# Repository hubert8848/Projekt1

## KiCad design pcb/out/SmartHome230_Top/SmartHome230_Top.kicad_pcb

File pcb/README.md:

# ⚡ pcbforge — generator schematów i PCB dla KiCad (A→Z)

Profesjonalny przepływ projektowania PCB sterowany opisem układu: **ty mówisz co chcesz
→ powstaje schemat KiCad bez błędów → płytka z footprintami i rozmieszczeniem →
eksport do autoroutingu (Freerouting) → gotowy projekt do otwarcia w KiCad.**
Do tego interfejs **web**, w którym uczysz toolkit, jakie footprinty i reguły
rozmieszczania stosować na przyszłość.

```
opis (czat / YAML)  ─►  Design (model)  ─►  .kicad_sch  (ERC czyste)
                                          ─►  .kicad_pcb (footprinty + placement)
                                          ─►  .dsn       (Specctra → Freerouting)
                          ▲                                   │
                          └──── baza wiedzy (kb.json) ◄────────┘  uczenie z web
```

## Dlaczego to działa bez instalacji KiCada
Toolkit generuje **samowystarczalne pliki KiCad 7**: wbudowane symbole + footprinty
i **jawną listę sieci** w PCB. Dzięki temu projekt otwiera się bez brakujących bibliotek.
Poprawność strukturalną potwierdza biblioteka `kiutils` (realny parser formatu KiCad),
a spójność elektryczną — wbudowane **ERC/DRC-lite**.

## Routing — czy trzeba uciekać z KiCada? Nie.
- **Ręcznie:** interaktywny router KiCada (push-and-shove) jest topowy — do większości
  płytek wystarcza i daje najlepszą jakość.
- **Automatycznie:** KiCad nie ma własnego autoroutera, ale **Freerouting** (Java)
  integruje się przez `.dsn` → trasowanie → `.ses`. To standardowa darmowa droga.
- **Inny program** (Altium/Allegro) ma sens dopiero przy bardzo gęstych, szybkich
  projektach (BGA, DDR, impedancja kontrolowana). Dla prototypów: KiCad + Freerouting.

pcbforge **eksportuje gotowy `.dsn`** i potrafi uruchomić Freerouting. Wynik `.ses`
wczytujesz w KiCad: **PCB Editor → File → Import → Specctra Session**.

---

## Szybki start

```bash
cd pcb
pip install -r requirements.txt          # opcjonalne (web/walidacja/YAML)

# 1) Wygeneruj przykładową płytkę ESP32 (kod):
python -m boards.esp32_devboard

# 2) Albo z deklaratywnego speca:
python -m pcbforge.cli build specs/ESP32_DevBoard.json
python -m pcbforge.cli check specs/ESP32_DevBoard.json
python -m pcbforge.cli route specs/ESP32_DevBoard.json --passes 20   # wymaga freerouting.jar

# 3) Podgląd graficzny (SVG/PNG, bez KiCada):
python -m pcbforge.cli preview specs/SmartSwitch.json

# 4) Pełna produkcja przez prawdziwy KiCad (Gerbery + STEP + ERC/DRC):
bash scripts/setup_kicad.sh                 # instaluje kicad-cli (raz na środowisko)
python -m pcbforge.cli fab specs/SmartSwitch.json

# 5) Interfejs web (przegląd + uczenie + podgląd inline + produkcja):
python -m web.app      # http://127.0.0.1:5000
```

> **KiCad:** eksport Gerberów/STEP/SVG działa od KiCad 7. **ERC/DRC z linii poleceń
> wymaga KiCad ≥ 8** — bez niego używane są kontrole wbudowane (`checks.py` + `rules.py`).

Pliki lądują w `pcb/out/<NazwaPłytki>/` — otwórz `*.kicad_pro` w KiCad.

## Autorouting — Freerouting
```bash
# pobierz jar z https://github.com/freerouting/freerouting/releases
export FREEROUTING_JAR=/sciezka/freerouting.jar
python -m pcbforge.cli route specs/ESP32_DevBoard.json
# -> out/ESP32_DevBoard/ESP32_DevBoard.ses  (import w KiCad)
```

---

## Katalog części
Obecnie ~35 części (rozszerzalne w `pcbforge/library/catalog.py`):
- **Bierne/dyskretne:** R, C, CP (elektrolit), L (cewki + cewka mocy 6×6), FB (ferryt),
  F (bezpiecznik), Y (kwarc), LED, diody (D_Schottky, D_Rectifier, D_TVS/ESD),
  tranzystory/MOSFETy (Q_NPN/PNP/NMOS/PMOS).
- **Układy:** ESP32-WROOM-32, AMS1117-3.3/5.0, MP1584 (buck), MCP23017 (ekspander I²C 16 IO),
  24LCxx (EEPROM), MAX485 (RS485), DS18B20 (czujnik temp 1-wire).
- **Złącza:** RJ45 8P8C, listwy zaciskowe, JST-XH, USB-C (zasilanie), USB Micro-B,
  gniazdo DC, goldpiny/sockety `Header_RxC` (też board-to-board), przyciski tact.
- **Obudowy footprintów:** chip 0402/0603/0805/1206, SOT-23-3/5/6, SOT-223, SOIC-8/14/16/28,
  TO-92, SMA/SOD-123/SOD-323, kwarc 3225 i in.

## Przykład: HomeController PRO — sterownik domowy 32 wej / 16 wyj
`boards/home_controller_pro.py` — pełny, realny produkt na 2 płytkach (24 V):
- **Dół:** zasilanie 24 V (bezpiecznik + dioda + MOV + buck 5 V + LDO 3V3), ekspander
  wyjść, **8× wyjście przekaźnikowe 230 V** + **8× wyjście MOSFET DC**, każde wyjście
  własny zacisk śrubowy; przekaźniki we wnętrzu (nie przy krawędzi).
- **Góra (węższa):** **ESP32-C3** + 2× ekspander I²C (**32 wejścia**), **8× RJ45** (wejścia,
  TVS na każde), **RS485 + CAN** (łączenie sterowników), złącze **TFT dotykowy**.
- Niezawodność „na 30 lat": TVS na każdym I/O, bezpiecznik + MOV, diody gasnące,
  pull-down bramek MOSFET, grube ścieżki + izolacja 230 V, dekapy, watchdog (ESP).

> ESP32-C3 ma mało GPIO — tu wykorzystane w pełni (USB do programowania, IO9 dzieli
> BOOT z CAN-RX). Pod pełną niezależność magistral rozważ **ESP32-S3**.

## Zasady rozmieszczania (urządzenia góra/dół, 230 V)
`boards/smart_home_230.py` + `pcbforge/layout.py` realizują zasady projektowe:
- **I/O na krawędziach** — złącza (USB-C, RJ45, zaciski) na górnej krawędzi; **strefa 230 V**
  (przekaźniki + zaciski sieciowe) na dolnej, z dala od logiki.
- **Otwory montażowe i złącze board-to-board w identycznych współrzędnych** na obu płytkach
  (wspólna `Frame`) — składają się 1:1.
- **Górna płytka węższa** o pasy I/O (góra/dół) — śrubokręt dochodzi do zacisków dolnej płytki
  (`Design.outline` = obszar środkowy).
- **Osobna dioda/TVS na każde I/O** (reguła `DIODE_PER_IO`).
- **230 V → grube ścieżki + izolacja**: sieci oznaczone `design.mark_mains(...)` dostają klasę
  `mains` w DSN (np. 1.5 mm / 2.5 mm creepage). Reguła `MAINS_UNMARKED` pilnuje oznaczenia.
- **Pasywne od spodu** — `c.side = "bottom"` (poprawne warstwy B.* + lustrzane pady).
- **Opisy po polsku** na silkscreenie (`Component.label`, `Design.notes`).

Nowe części: **przekaźnik SPDT** (szerokie pady 230 V), **otwór montażowy M3**, sterownik
przekaźnika (blok `relay_driver`: tranzystor + dioda gasnąca + rezystor bazy).

## Przykład: urządzenie dwupłytkowe (góra/dół)
`boards/home_controller.py` — **kontroler automatyki domowej z dwóch PCB** łączonych
listwą board-to-board 2×10 (wspólne mapowanie pinów `B2B_MAP`):
- **Dół** (`HomeCtrl_Bottom`): wejście 12 V (listwa) → bezpiecznik + dioda zabezpieczająca
  → **buck MP1584 (5 V)** z cewką/diodą/dzielnikiem → **LDO AMS1117 (3V3)** → **ESP32**.
- **Góra** (`HomeCtrl_Top`): listwa B2B → **MCP23017** (16 wejść przycisków) → **4× RJ45**
  (przyciski ścienne + 1-wire), **DS18B20** (temperatura), **ochrona ESD (TVS)** i pull-upy.

RJ45 użyte jako **złącze okablowania** (cat-kabel do włączników i czujnika), bez magnetyki/PHY.
Obie płytki: **ERC 0 błędów, 0 ostrzeżeń**, zwalidowane `kiutils`.

## Przykład: ESP32-WROOM-32 DevBoard
Pełny, realny układ wygenerowany end-to-end (`boards/esp32_devboard.py`):
zasilanie USB 5 V → LDO **AMS1117-3.3** → 3V3, kondensatory bulk + odsprzęgające,
pull-upy EN/IO0, przyciski **EN/BOOT**, LED statusu na IO2, header programatora
1×6 (GND/3V3/EN/IO0/TX/RX) i breakout GPIO 1×10. **ERC: 0 błędów, 0 ostrzeżeń.**

## Opis płytki w YAML/JSON
```yaml
name: Migacz_555
components:
  - {ref: U1, part: NE555, footprint: ... , connections: {...}}
  - {ref: R1, part: R, value: 10k, connections: {"1": VCC, "2": THR}}
```
(rdzeń biblioteki części rozszerza się w `pcbforge/library/catalog.py`)

## Uczenie (baza wiedzy)
W web, na stronie płytki:
- **Zmień footprint części** → zapis do `knowledge/kb.json`, stosowany przy kolejnych generacjach.
- **Reguła „near"** → „umieść C3 blisko U1 o 3 mm" (autoplacement to uwzględni, jeśli nie powoduje kolizji).
- **Notatki** → wskazówki na przyszłość.

---

## Architektura
| Plik | Rola |
|---|---|
| `pcbforge/model.py` | model: `Component`, `Net`, `Design`, reguły |
| `pcbforge/library/symbols.py` | generatory symboli schematu (geometria pinów) |
| `pcbforge/library/footprints.py` | generatory footprintów (pady, kontur) |
| `pcbforge/library/catalog.py` | katalog części (symbol + footprint + piny) |
| `pcbforge/sch_writer.py` | `.kicad_sch` — symbole, etykiety sieci, PWR_FLAG |
| `pcbforge/pcb_writer.py` | `.kicad_pcb` — footprinty, jawna netlista, obrys |
| `pcbforge/placement.py` | autoplacement (pakowanie półkowe, bez kolizji) |
| `pcbforge/checks.py` | ERC + DRC-lite (bez KiCada) |
| `pcbforge/freerouting.py` | eksport `.dsn` + uruchamianie autoroutera |
| `pcbforge/knowledge.py` | baza wiedzy (uczone footprinty/reguły) |
| `pcbforge/spec.py` | deklaratywny opis płytki ↔ model |
| `web/` | interfejs przeglądu i uczenia |
| `boards/`, `specs/` | przykładowe płytki |

## Testy
```bash
python tests/test_build.py     # 6/6: S-expression, netlista, ERC, spójność pin↔pad
```

## Ograniczenia i plan rozwoju
- Biblioteka części jest celowo niewielka (R/C/LED/D/ESP32/AMS1117/USB/przyciski/goldpiny) —
  rozszerzamy „na życzenie" w czacie (ty mówisz część → dodaję symbol+footprint).
- Autoplacement jest bezkolizyjny, ale nie „produkcyjny" — reguły z bazy wiedzy go dostrajają.
- Import `.ses` (trasy) robi KiCad jednym kliknięciem; bezpośredni zapis tras do `.kicad_pcb`
  jest na liście „do zrobienia".
- Przy zainstalowanym `kicad-cli` można dołożyć **prawdziwe ERC/DRC/Gerbery/3D**.

> Format docelowy: **KiCad 7** (`.kicad_sch` v20230121, `.kicad_pcb` v20221018).
> Pliki otwiera też KiCad 8/9.

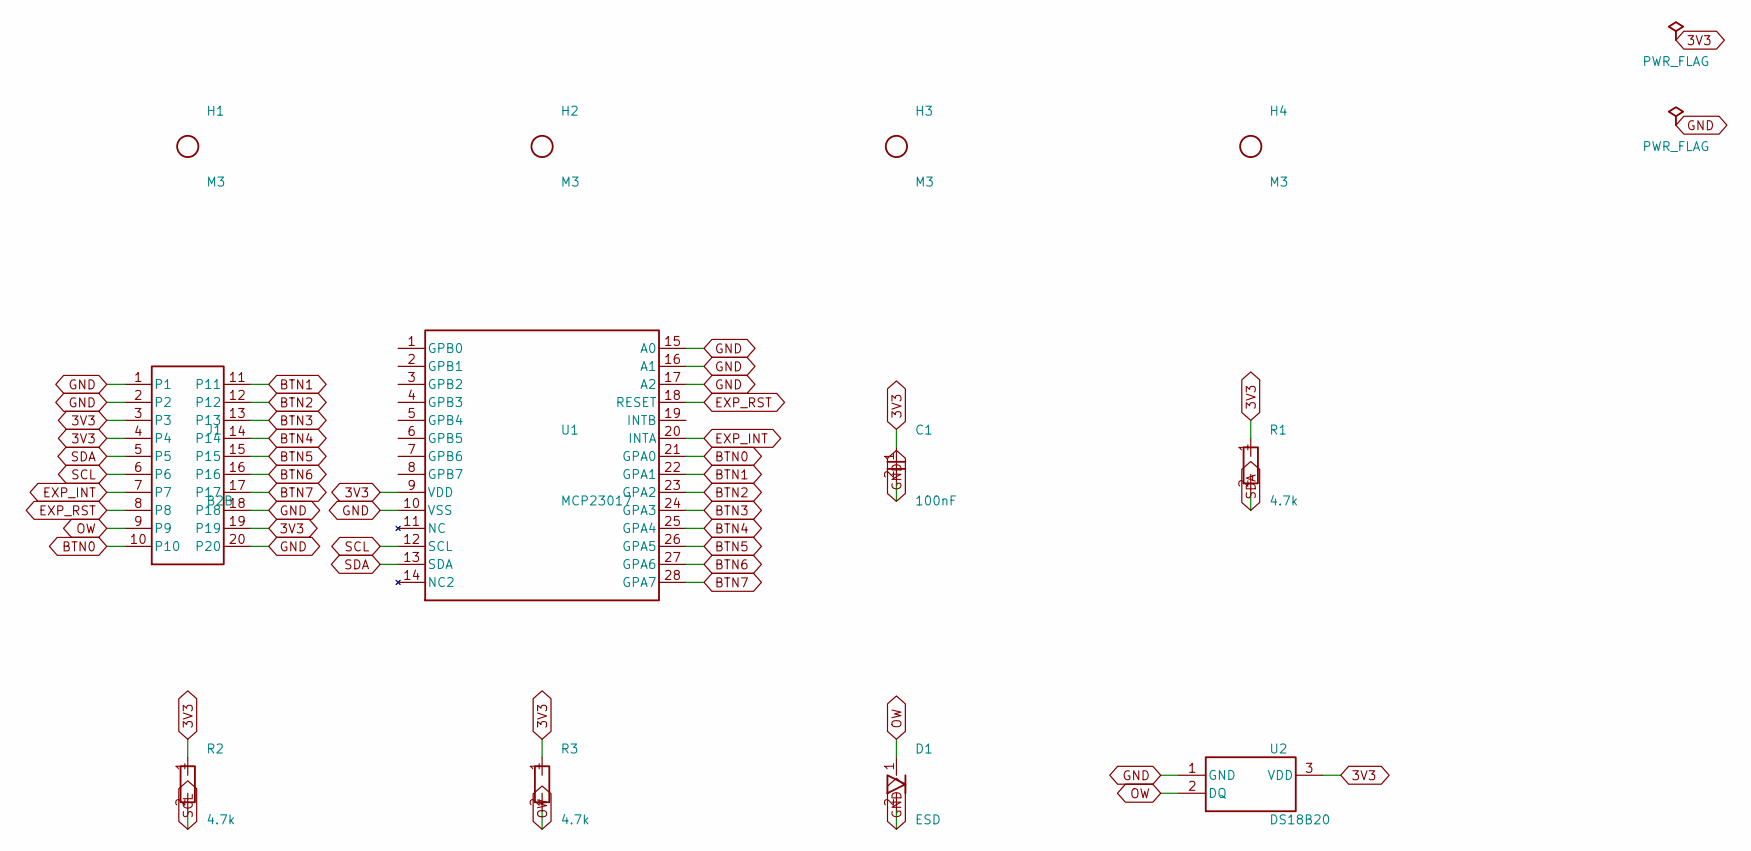
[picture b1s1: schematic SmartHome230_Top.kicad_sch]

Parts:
C1: 100nF; C_0805
D1: ESD; D_SOD-323
H1, H2, H3, H4: M3; MountingHole_M3
J1: B2B; Header_2x10
R1, R2, R3: 4.7k; R_0805
U1: MCP23017; SOIC-28
U2: DS18B20; TO-92

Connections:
3V3: C1.1, J1.3, J1.4, J1.19, R1.1, R2.1, R3.1, U1.9 (VDD), U2.3 (VDD)
BTN0: J1.10, U1.21 (GPA0)
BTN1: J1.11, U1.22 (GPA1)
BTN2: J1.12, U1.23 (GPA2)
BTN3: J1.13, U1.24 (GPA3)
BTN4: J1.14, U1.25 (GPA4)
BTN5: J1.15, U1.26 (GPA5)
BTN6: J1.16, U1.27 (GPA6)
BTN7: J1.17, U1.28 (GPA7)
EXP_INT: J1.7, U1.20 (INTA)
EXP_RST: J1.8, U1.18 (RESET)
GND: C1.2, D1.2, J1.1, J1.2, J1.18, J1.20, U1.10 (VSS), U1.15 (A0), U1.16 (A1), U1.17 (A2), U2.1 (GND)
OW: D1.1, J1.9, R3.2, U2.2 (DQ)
SCL: J1.6, R2.2, U1.12 (SCL)
SDA: J1.5, R1.2, U1.13 (SDA)

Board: 2 copper layers, 12 parts (4 on the bottom side), 15 nets, no tracks yet.

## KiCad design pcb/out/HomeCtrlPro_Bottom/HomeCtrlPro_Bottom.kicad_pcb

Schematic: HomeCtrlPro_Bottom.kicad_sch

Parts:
C1, C3: 100uF; CP_1206
C2: 10nF; C_0805
C4: 47uF; CP_1206
C5, C6, C9, C10, C11, C12, C13, C14, C15, C16, C17, C18, C19: 100nF; C_0805
C7, C8: 10uF; CP_1206
D1, D2, D11, D13, D15, D17, D19, D21, D23, D25: SS34; D_SMA
D3, D4, D5, D6, D7, D8, D9, D10: 1N4148; D_SMA
D12, D14, D16, D18, D20, D22, D24, D26: TVS; D_SOD-323
F1: 3A; F_1206
F2, F3, F4, F5, F6, F7, F8, F9: 0.5A; PTC_1812
F10, F11, F12, F13, F14, F15, F16, F17: 2A; PTC_1812
H1, H2, H3, H4: M3; MountingHole_M3
J1: B2B; Header_2x10
J2: 24V; ScrewTerminal_1x02
J3: 230V; ScrewTerminal_1x03
J4: OUT0; ScrewTerminal_1x02
J5: OUT1; ScrewTerminal_1x02
J6: OUT2; ScrewTerminal_1x02
J7: OUT3; ScrewTerminal_1x02
J8: OUT4; ScrewTerminal_1x02
J9: OUT5; ScrewTerminal_1x02
J10: OUT6; ScrewTerminal_1x02
J11: OUT7; ScrewTerminal_1x02
J12: OUTDC8; ScrewTerminal_1x02
J13: OUTDC9; ScrewTerminal_1x02
J14: OUTDC10; ScrewTerminal_1x02
J15: OUTDC11; ScrewTerminal_1x02
J16: OUTDC12; ScrewTerminal_1x02
J17: OUTDC13; ScrewTerminal_1x02
J18: OUTDC14; ScrewTerminal_1x02
J19: OUTDC15; ScrewTerminal_1x02
K1, K2, K3, K4, K5, K6, K7, K8: SRD-24V; Relay_SPDT_SRD
L1: 10uH; L_6x6
LED1, LED2, LED3, LED4, LED5, LED6, LED7, LED8, LED9, LED10, LED11, LED12, LED13, LED14, LED15, LED16: ON; LED_0805
Q1, Q2, Q3, Q4, Q5, Q6, Q7, Q8: BC547; SOT-23-3
Q9, Q10, Q11, Q12, Q13, Q14, Q15, Q16: IRLZ44N; TO-252
R1, R28, R31, R34, R37, R40, R43, R46, R49: 100k; R_0805
R2: 20k; R_0805
R3, R4, R6, R7, R9, R10, R12, R13, R15, R16, R18, R19, R21, R22, R24, R25, R29, R32, R35, R38, R41, R44, R47, R50: 1k; R_0805
R5, R8, R11, R14, R17, R20, R23, R26, R27, R30, R33, R36, R39, R42, R45, R48: 100; R_0805
RV1: S14K30; MOV_Disc
RV2, RV3, RV4, RV5, RV6, RV7, RV8, RV9: S14K275; MOV_Disc
U1: MP1584; SOIC-8
U2: AMS1117-3.3; SOT-223
U3: MCP23017; SOIC-28

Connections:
3V3: C8.1, C10.1, C11.1, J1.3, J1.4, J1.9, J1.12, J1.14, J1.16, J1.18, U2.2 (VOUT), U2.4 (VOUT(tab)), U3.9 (VDD), U3.17 (A2)
EXP_RST: J1.7, U3.18 (RESET)
GND: C1.2, C3.2, C4.2, C5.2, C6.2, C7.2, C8.2, C9.2, C10.2, C11.2, D2.1, D12.2, D14.2, D16.2, D18.2, D20.2, D22.2, D24.2, D26.2, J1.1, J1.2, J1.8, J1.10, J1.11, J1.13, J1.15, J1.17, J1.19, J1.20, J2.2, LED1.2, LED2.2, LED3.2, LED4.2, LED5.2, LED6.2, LED7.2, LED8.2, LED9.2, LED10.2, LED11.2, LED12.2, LED13.2, LED14.2, LED15.2, LED16.2, Q1.3 (E), Q2.3 (E), Q3.3 (E), Q4.3 (E), Q5.3 (E), Q6.3 (E), Q7.3 (E), Q8.3 (E), Q9.3 (S), Q10.3 (S), Q11.3 (S), Q12.3 (S), Q13.3 (S), Q14.3 (S), Q15.3 (S), Q16.3 (S), R2.2, R28.2, R31.2, R34.2, R37.2, R40.2, R43.2, R46.2, R49.2, RV1.2, U1.4 (GND), U2.1 (GND), U3.10 (VSS), U3.15 (A0), U3.16 (A1)
L: J3.1, K1.4 (COM), K2.4 (COM), K3.4 (COM), K4.4 (COM), K5.4 (COM), K6.4 (COM), K7.4 (COM), K8.4 (COM), R5.1, R8.1, R11.1, R14.1, R17.1, R20.1, R23.1, R26.1
LAMP0: F2.2, J4.1, RV2.1
LAMP1: F3.2, J5.1, RV3.1
LAMP2: F4.2, J6.1, RV4.1
LAMP3: F5.2, J7.1, RV5.1
LAMP4: F6.2, J8.1, RV6.1
LAMP5: F7.2, J9.1, RV7.1
LAMP6: F8.2, J10.1, RV8.1
LAMP7: F9.2, J11.1, RV9.1
N: J3.2, J4.2, J5.2, J6.2, J7.2, J8.2, J9.2, J10.2, J11.2, RV2.2, RV3.2, RV4.2, RV5.2, RV6.2, RV7.2, RV8.2, RV9.2
OUT0: R3.1, R4.1, U3.21 (GPA0)
OUT1: R6.1, R7.1, U3.22 (GPA1)
OUT2: R9.1, R10.1, U3.23 (GPA2)
OUT3: R12.1, R13.1, U3.24 (GPA3)
OUT4: R15.1, R16.1, U3.25 (GPA4)
OUT5: R18.1, R19.1, U3.26 (GPA5)
OUT6: R21.1, R22.1, U3.27 (GPA6)
OUT7: R24.1, R25.1, U3.28 (GPA7)
OUT8: R27.1, R29.1, U3.1 (GPB0)
OUT9: R30.1, R32.1, U3.2 (GPB1)
OUT10: R33.1, R35.1, U3.3 (GPB2)
OUT11: R36.1, R38.1, U3.4 (GPB3)
OUT12: R39.1, R41.1, U3.5 (GPB4)
OUT13: R42.1, R44.1, U3.6 (GPB5)
OUT14: R45.1, R47.1, U3.7 (GPB6)
OUT15: R48.1, R50.1, U3.8 (GPB7)
OUTDC8: D12.1, F10.2, J12.2
OUTDC9: D14.1, F11.2, J13.2
OUTDC10: D16.1, F12.2, J14.2
OUTDC11: D18.1, F13.2, J15.2
OUTDC12: D20.1, F14.2, J16.2
OUTDC13: D22.1, F15.2, J17.2
OUTDC14: D24.1, F16.2, J18.2
OUTDC15: D26.1, F17.2, J19.2
PE: H1.1, H2.1, H3.1, H4.1, J3.3
SCL: J1.6, U3.12 (SCL)
SDA: J1.5, U3.13 (SDA)
V5: C4.1, C6.1, C7.1, C9.1, L1.2, R1.1, U2.3 (VIN)
V24: F1.1, J2.1
V24P: C1.1, C3.1, C5.1, D1.2, D3.2, D4.2, D5.2, D6.2, D7.2, D8.2, D9.2, D10.2, D11.2, D13.2, D15.2, D17.2, D19.2, D21.2, D23.2, D25.2, J12.1, J13.1, J14.1, J15.1, J16.1, J17.1, J18.1, J19.1, K1.1 (COIL+), K2.1 (COIL+), K3.1 (COIL+), K4.1 (COIL+), K5.1 (COIL+), K6.1 (COIL+), K7.1 (COIL+), K8.1 (COIL+), RV1.1, U1.2 (VIN), U1.7 (EN)
_BST_V5: C2.1, U1.1 (BST)
_DRN8: D11.1, F10.1, Q9.2 (D)
_DRN9: D13.1, F11.1, Q10.2 (D)
_DRN10: D15.1, F12.1, Q11.2 (D)
_DRN11: D17.1, F13.1, Q12.2 (D)
_DRN12: D19.1, F14.1, Q13.2 (D)
_DRN13: D21.1, F15.1, Q14.2 (D)
_DRN14: D23.1, F16.1, Q15.2 (D)
_DRN15: D25.1, F17.1, Q16.2 (D)
_FB_V5: R1.2, R2.1, U1.5 (FB)
_FUSED_V24P: D1.1, F1.2
_G8: Q9.1 (G), R27.2, R28.1
_G9: Q10.1 (G), R30.2, R31.1
_G10: Q11.1 (G), R33.2, R34.1
_G11: Q12.1 (G), R36.2, R37.1
_G12: Q13.1 (G), R39.2, R40.1
_G13: Q14.1 (G), R42.2, R43.1
_G14: Q15.1 (G), R45.2, R46.1
_G15: Q16.1 (G), R48.2, R49.1
_ML8: LED9.1, R29.2
_ML9: LED10.1, R32.2
_ML10: LED11.1, R35.2
_ML11: LED12.1, R38.2
_ML12: LED13.1, R41.2
_ML13: LED14.1, R44.2
_ML14: LED15.1, R47.2
_ML15: LED16.1, R50.2
_NO0: C12.2, F2.1, K1.3 (NO)
_NO1: C13.2, F3.1, K2.3 (NO)
_NO2: C14.2, F4.1, K3.3 (NO)
_NO3: C15.2, F5.1, K4.3 (NO)
_NO4: C16.2, F6.1, K5.3 (NO)
_NO5: C17.2, F7.1, K6.3 (NO)
_NO6: C18.2, F8.1, K7.3 (NO)
_NO7: C19.2, F9.1, K8.3 (NO)
_RB0: Q1.1 (B), R3.2
_RB1: Q2.1 (B), R6.2
_RB2: Q3.1 (B), R9.2
_RB3: Q4.1 (B), R12.2
_RB4: Q5.1 (B), R15.2
_RB5: Q6.1 (B), R18.2
_RB6: Q7.1 (B), R21.2
_RB7: Q8.1 (B), R24.2
_RC0: D3.1, K1.2 (COIL-), Q1.2 (C)
_RC1: D4.1, K2.2 (COIL-), Q2.2 (C)
_RC2: D5.1, K3.2 (COIL-), Q3.2 (C)
_RC3: D6.1, K4.2 (COIL-), Q4.2 (C)
_RC4: D7.1, K5.2 (COIL-), Q5.2 (C)
_RC5: D8.1, K6.2 (COIL-), Q6.2 (C)
_RC6: D9.1, K7.2 (COIL-), Q7.2 (C)
_RC7: D10.1, K8.2 (COIL-), Q8.2 (C)
_RL0: LED1.1, R4.2
_RL1: LED2.1, R7.2
_RL2: LED3.1, R10.2
_RL3: LED4.1, R13.2
_RL4: LED5.1, R16.2
_RL5: LED6.1, R19.2
_RL6: LED7.1, R22.2
_RL7: LED8.1, R25.2
_SN0: C12.1, R5.2
_SN1: C13.1, R8.2
_SN2: C14.1, R11.2
_SN3: C15.1, R14.2
_SN4: C16.1, R17.2
_SN5: C17.1, R20.2
_SN6: C18.1, R23.2
_SN7: C19.1, R26.2
_SW_V5: C2.2, D2.2, L1.1, U1.3 (SW)

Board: 2 copper layers, 188 parts (0 on the bottom side), 111 nets, no tracks yet.

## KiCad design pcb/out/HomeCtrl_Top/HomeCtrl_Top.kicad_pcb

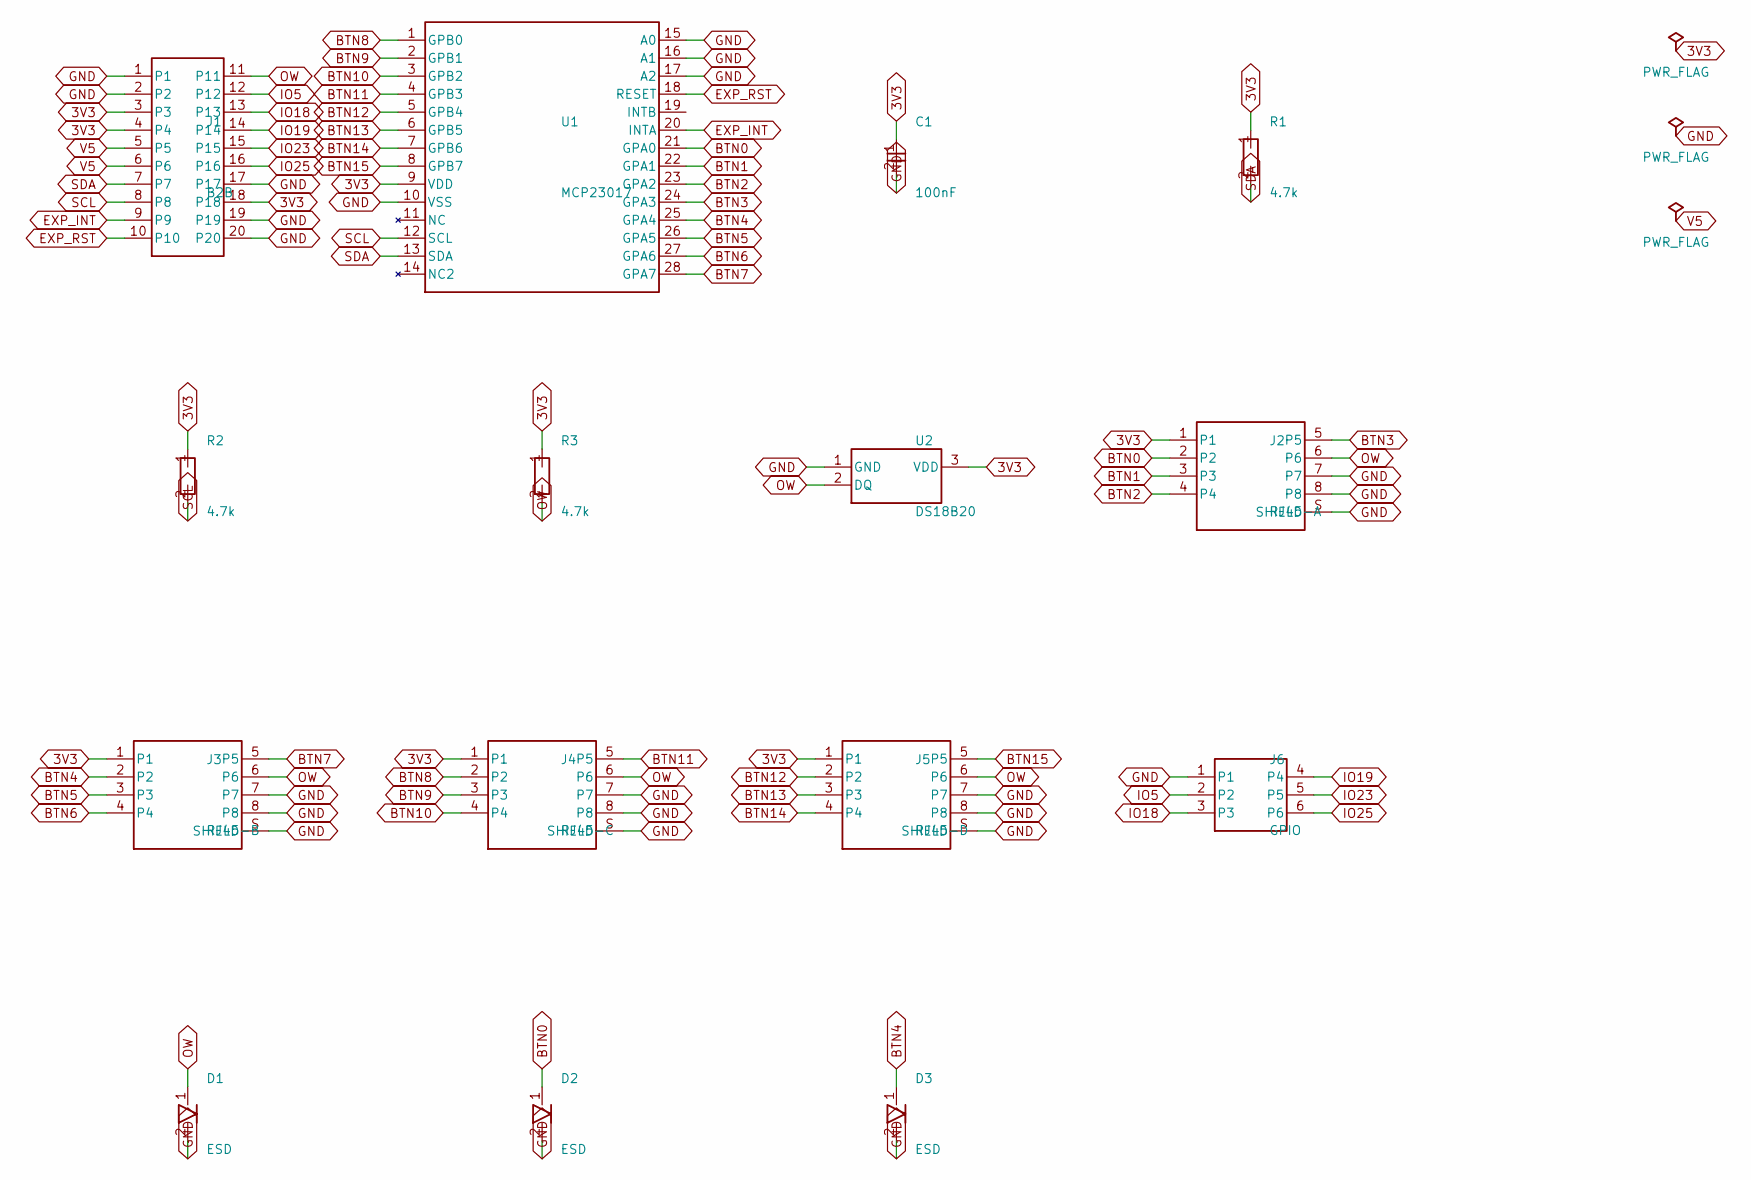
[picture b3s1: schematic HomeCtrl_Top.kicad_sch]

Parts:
C1: 100nF; C_0805
D1, D2, D3: ESD; D_SOD-323
J1: B2B; Header_2x10
J2: RJ45-A; RJ45_8P8C
J3: RJ45-B; RJ45_8P8C
J4: RJ45-C; RJ45_8P8C
J5: RJ45-D; RJ45_8P8C
J6: GPIO; Header_1x06
R1, R2, R3: 4.7k; R_0805
U1: MCP23017; SOIC-28
U2: DS18B20; TO-92

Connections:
3V3: C1.1, J1.3, J1.4, J1.18, J2.1, J3.1, J4.1, J5.1, R1.1, R2.1, R3.1, U1.9 (VDD), U2.3 (VDD)
BTN0: D2.1, J2.2, U1.21 (GPA0)
BTN1: J2.3, U1.22 (GPA1)
BTN2: J2.4, U1.23 (GPA2)
BTN3: J2.5, U1.24 (GPA3)
BTN4: D3.1, J3.2, U1.25 (GPA4)
BTN5: J3.3, U1.26 (GPA5)
BTN6: J3.4, U1.27 (GPA6)
BTN7: J3.5, U1.28 (GPA7)
BTN8: J4.2, U1.1 (GPB0)
BTN9: J4.3, U1.2 (GPB1)
BTN10: J4.4, U1.3 (GPB2)
BTN11: J4.5, U1.4 (GPB3)
BTN12: J5.2, U1.5 (GPB4)
BTN13: J5.3, U1.6 (GPB5)
BTN14: J5.4, U1.7 (GPB6)
BTN15: J5.5, U1.8 (GPB7)
EXP_INT: J1.9, U1.20 (INTA)
EXP_RST: J1.10, U1.18 (RESET)
GND: C1.2, D1.2, D2.2, D3.2, J1.1, J1.2, J1.17, J1.19, J1.20, J2.7, J2.8, J2.S (SHIELD), J3.7, J3.8, J3.S (SHIELD), J4.7, J4.8, J4.S (SHIELD), J5.7, J5.8, J5.S (SHIELD), J6.1, U1.10 (VSS), U1.15 (A0), U1.16 (A1), U1.17 (A2), U2.1 (GND)
IO5: J1.12, J6.2
IO18: J1.13, J6.3
IO19: J1.14, J6.4
IO23: J1.15, J6.5
IO25: J1.16, J6.6
OW: D1.1, J1.11, J2.6, J3.6, J4.6, J5.6, R3.2, U2.2 (DQ)
SCL: J1.8, R2.2, U1.12 (SCL)
SDA: J1.7, R1.2, U1.13 (SDA)
V5: J1.5, J1.6

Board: 2 copper layers, 15 parts (0 on the bottom side), 29 nets, no tracks yet.

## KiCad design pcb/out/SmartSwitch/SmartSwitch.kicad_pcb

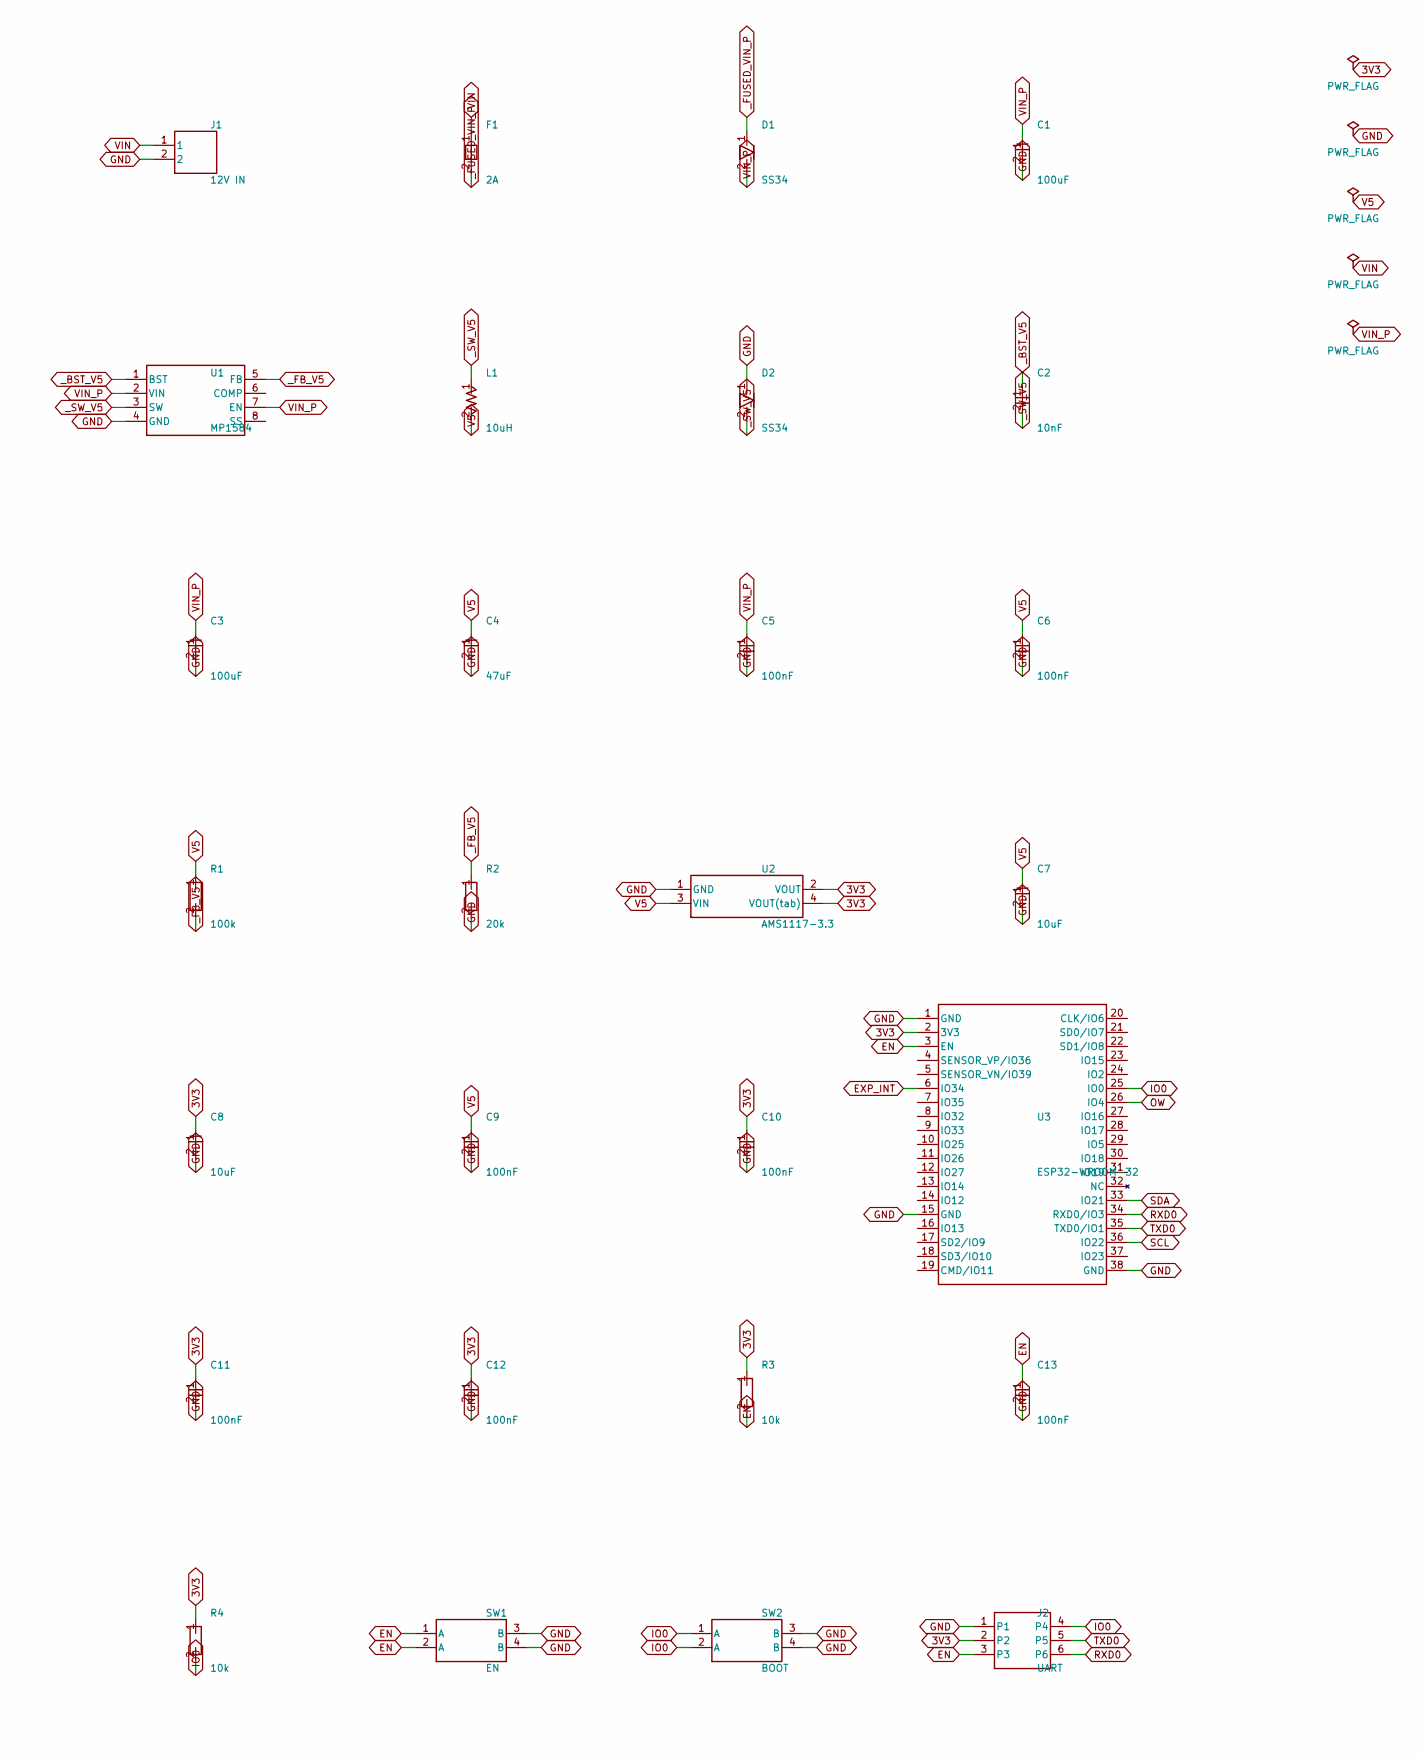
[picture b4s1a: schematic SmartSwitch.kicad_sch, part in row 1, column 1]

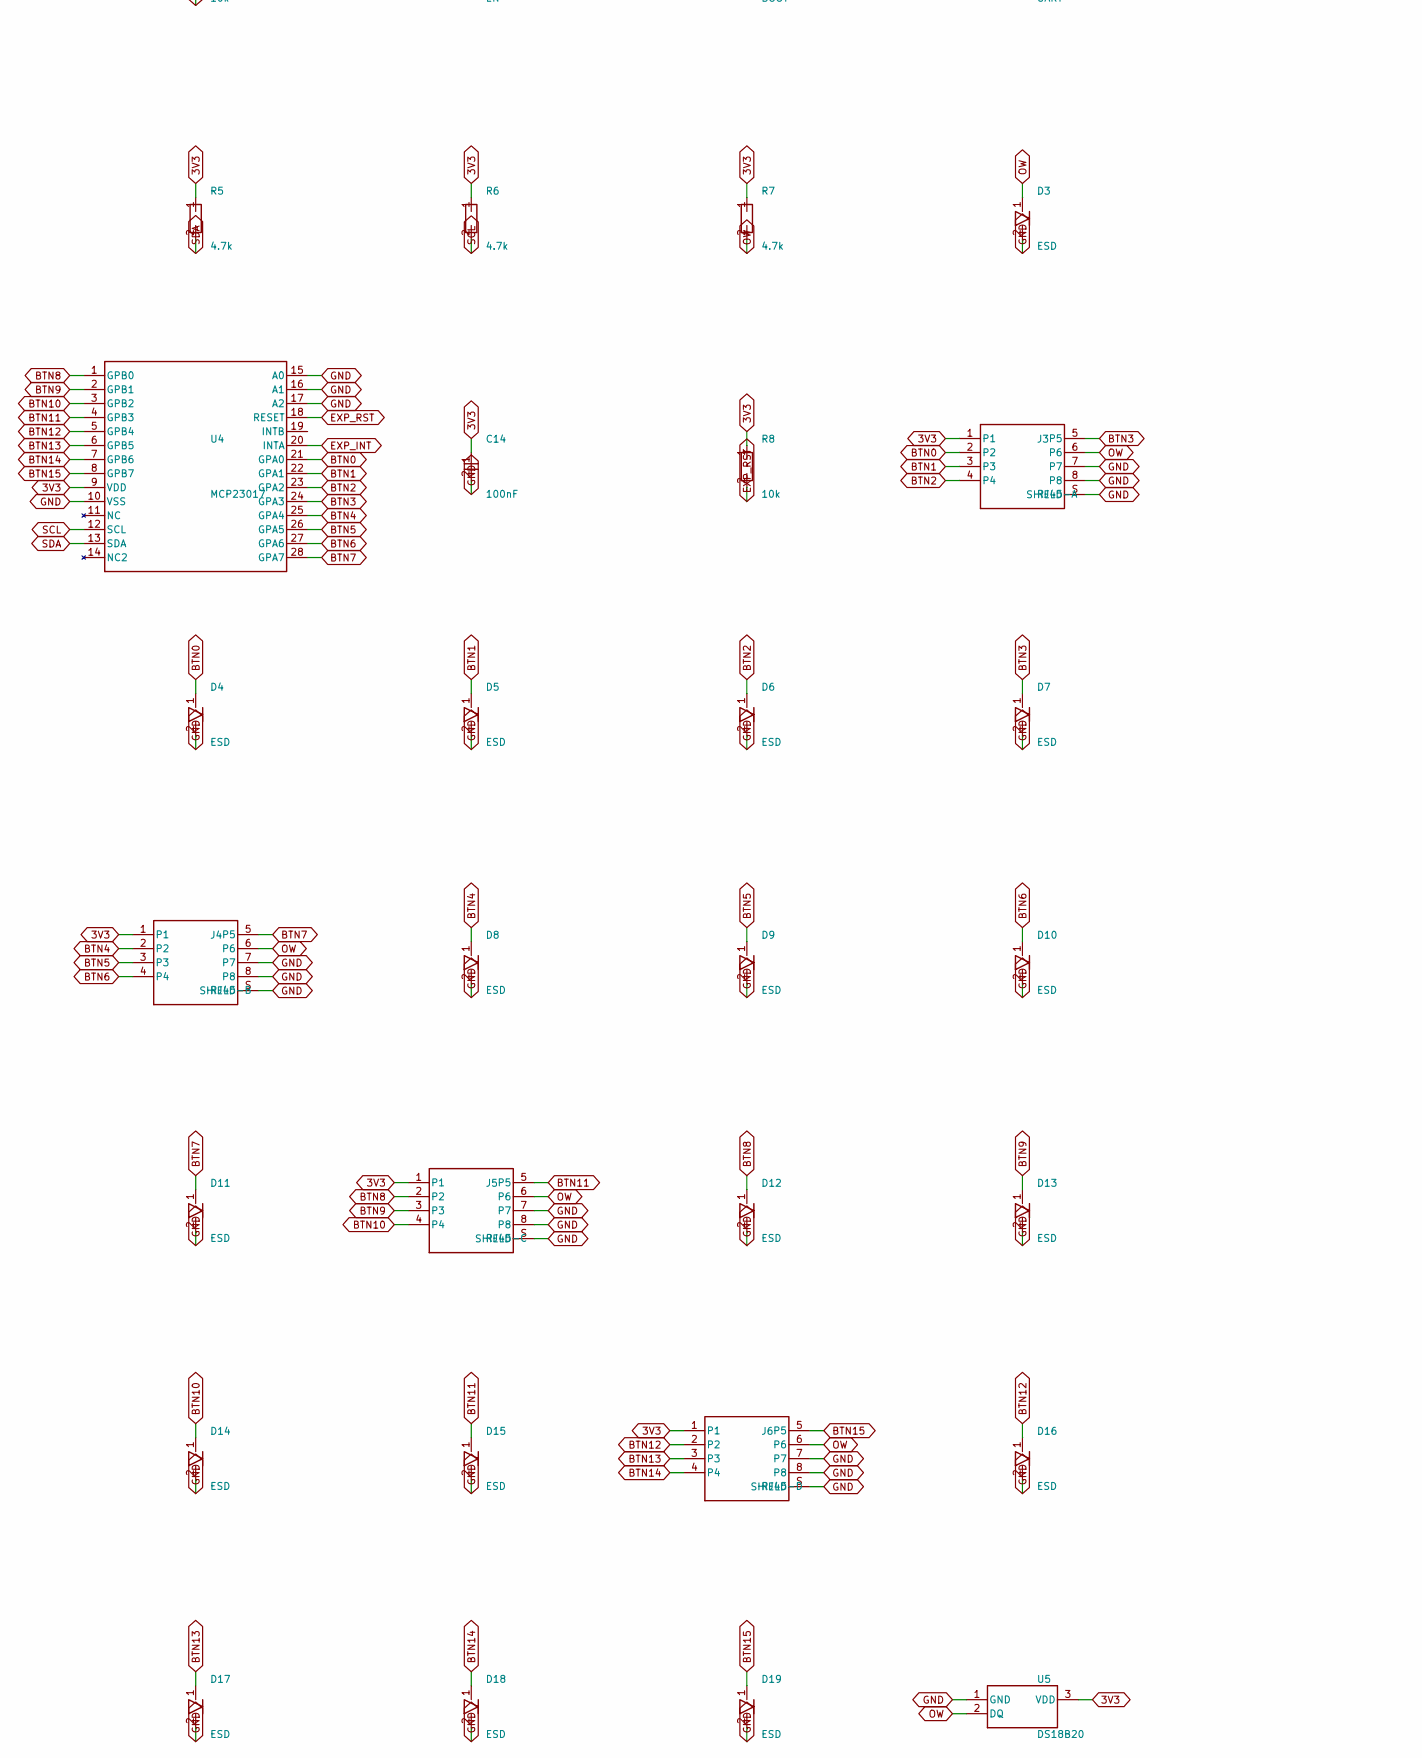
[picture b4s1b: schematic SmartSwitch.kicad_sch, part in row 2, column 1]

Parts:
C1, C3: 100uF; CP_1206
C2: 10nF; C_0805
C4: 47uF; CP_1206
C5, C6, C9, C10, C11, C12, C13, C14: 100nF; C_0805
C7, C8: 10uF; CP_1206
D1, D2: SS34; D_SMA
D3, D4, D5, D6, D7, D8, D9, D10, D11, D12, D13, D14, D15, D16, D17, D18, D19: ESD; D_SOD-323
F1: 2A; F_1206
J1: 12V IN; ScrewTerminal_1x02
J2: UART; Header_1x06
J3: RJ45-A; RJ45_8P8C
J4: RJ45-B; RJ45_8P8C
J5: RJ45-C; RJ45_8P8C
J6: RJ45-D; RJ45_8P8C
L1: 10uH; L_6x6
R1: 100k; R_0805
R2: 20k; R_0805
R3, R4, R8: 10k; R_0805
R5, R6, R7: 4.7k; R_0805
SW1: EN; SW_Push_6mm
SW2: BOOT; SW_Push_6mm
U1: MP1584; SOIC-8
U2: AMS1117-3.3; SOT-223
U3: ESP32-WROOM-32
U4: MCP23017; SOIC-28
U5: DS18B20; TO-92

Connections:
3V3: C8.1, C10.1, C11.1, C12.1, C14.1, J2.2, J3.1, J4.1, J5.1, J6.1, R3.1, R4.1, R5.1, R6.1, R7.1, R8.1, U2.2 (VOUT), U2.4 (VOUT(tab)), U3.2 (3V3), U4.9 (VDD), U5.3 (VDD)
BTN0: D4.1, J3.2, U4.21 (GPA0)
BTN1: D5.1, J3.3, U4.22 (GPA1)
BTN2: D6.1, J3.4, U4.23 (GPA2)
BTN3: D7.1, J3.5, U4.24 (GPA3)
BTN4: D8.1, J4.2, U4.25 (GPA4)
BTN5: D9.1, J4.3, U4.26 (GPA5)
BTN6: D10.1, J4.4, U4.27 (GPA6)
BTN7: D11.1, J4.5, U4.28 (GPA7)
BTN8: D12.1, J5.2, U4.1 (GPB0)
BTN9: D13.1, J5.3, U4.2 (GPB1)
BTN10: D14.1, J5.4, U4.3 (GPB2)
BTN11: D15.1, J5.5, U4.4 (GPB3)
BTN12: D16.1, J6.2, U4.5 (GPB4)
BTN13: D17.1, J6.3, U4.6 (GPB5)
BTN14: D18.1, J6.4, U4.7 (GPB6)
BTN15: D19.1, J6.5, U4.8 (GPB7)
EN: C13.1, J2.3, R3.2, SW1.1 (A), SW1.2 (A), U3.3 (EN)
EXP_INT: U3.6 (IO34), U4.20 (INTA)
EXP_RST: R8.2, U4.18 (RESET)
GND: C1.2, C3.2, C4.2, C5.2, C6.2, C7.2, C8.2, C9.2, C10.2, C11.2, C12.2, C13.2, C14.2, D2.1, D3.2, D4.2, D5.2, D6.2, D7.2, D8.2, D9.2, D10.2, D11.2, D12.2, D13.2, D14.2, D15.2, D16.2, D17.2, D18.2, D19.2, J1.2, J2.1, J3.7, J3.8, J3.S (SHIELD), J4.7, J4.8, J4.S (SHIELD), J5.7, J5.8, J5.S (SHIELD), J6.7, J6.8, J6.S (SHIELD), R2.2, SW1.3 (B), SW1.4 (B), SW2.3 (B), SW2.4 (B), U1.4 (GND), U2.1 (GND), U3.1 (GND), U3.15 (GND), U3.38 (GND), U4.10 (VSS), U4.15 (A0), U4.16 (A1), U4.17 (A2), U5.1 (GND)
IO0: J2.4, R4.2, SW2.1 (A), SW2.2 (A), U3.25 (IO0)
OW: D3.1, J3.6, J4.6, J5.6, J6.6, R7.2, U3.26 (IO4), U5.2 (DQ)
RXD0: J2.6, U3.34 (RXD0/IO3)
SCL: R6.2, U3.36 (IO22), U4.12 (SCL)
SDA: R5.2, U3.33 (IO21), U4.13 (SDA)
TXD0: J2.5, U3.35 (TXD0/IO1)
V5: C4.1, C6.1, C7.1, C9.1, L1.2, R1.1, U2.3 (VIN)
VIN: F1.1, J1.1
VIN_P: C1.1, C3.1, C5.1, D1.2, U1.2 (VIN), U1.7 (EN)
_BST_V5: C2.1, U1.1 (BST)
_FB_V5: R1.2, R2.1, U1.5 (FB)
_FUSED_VIN_P: D1.1, F1.2
_SW_V5: C2.2, D2.2, L1.1, U1.3 (SW)

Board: 2 copper layers, 56 parts (0 on the bottom side), 34 nets, no tracks yet.

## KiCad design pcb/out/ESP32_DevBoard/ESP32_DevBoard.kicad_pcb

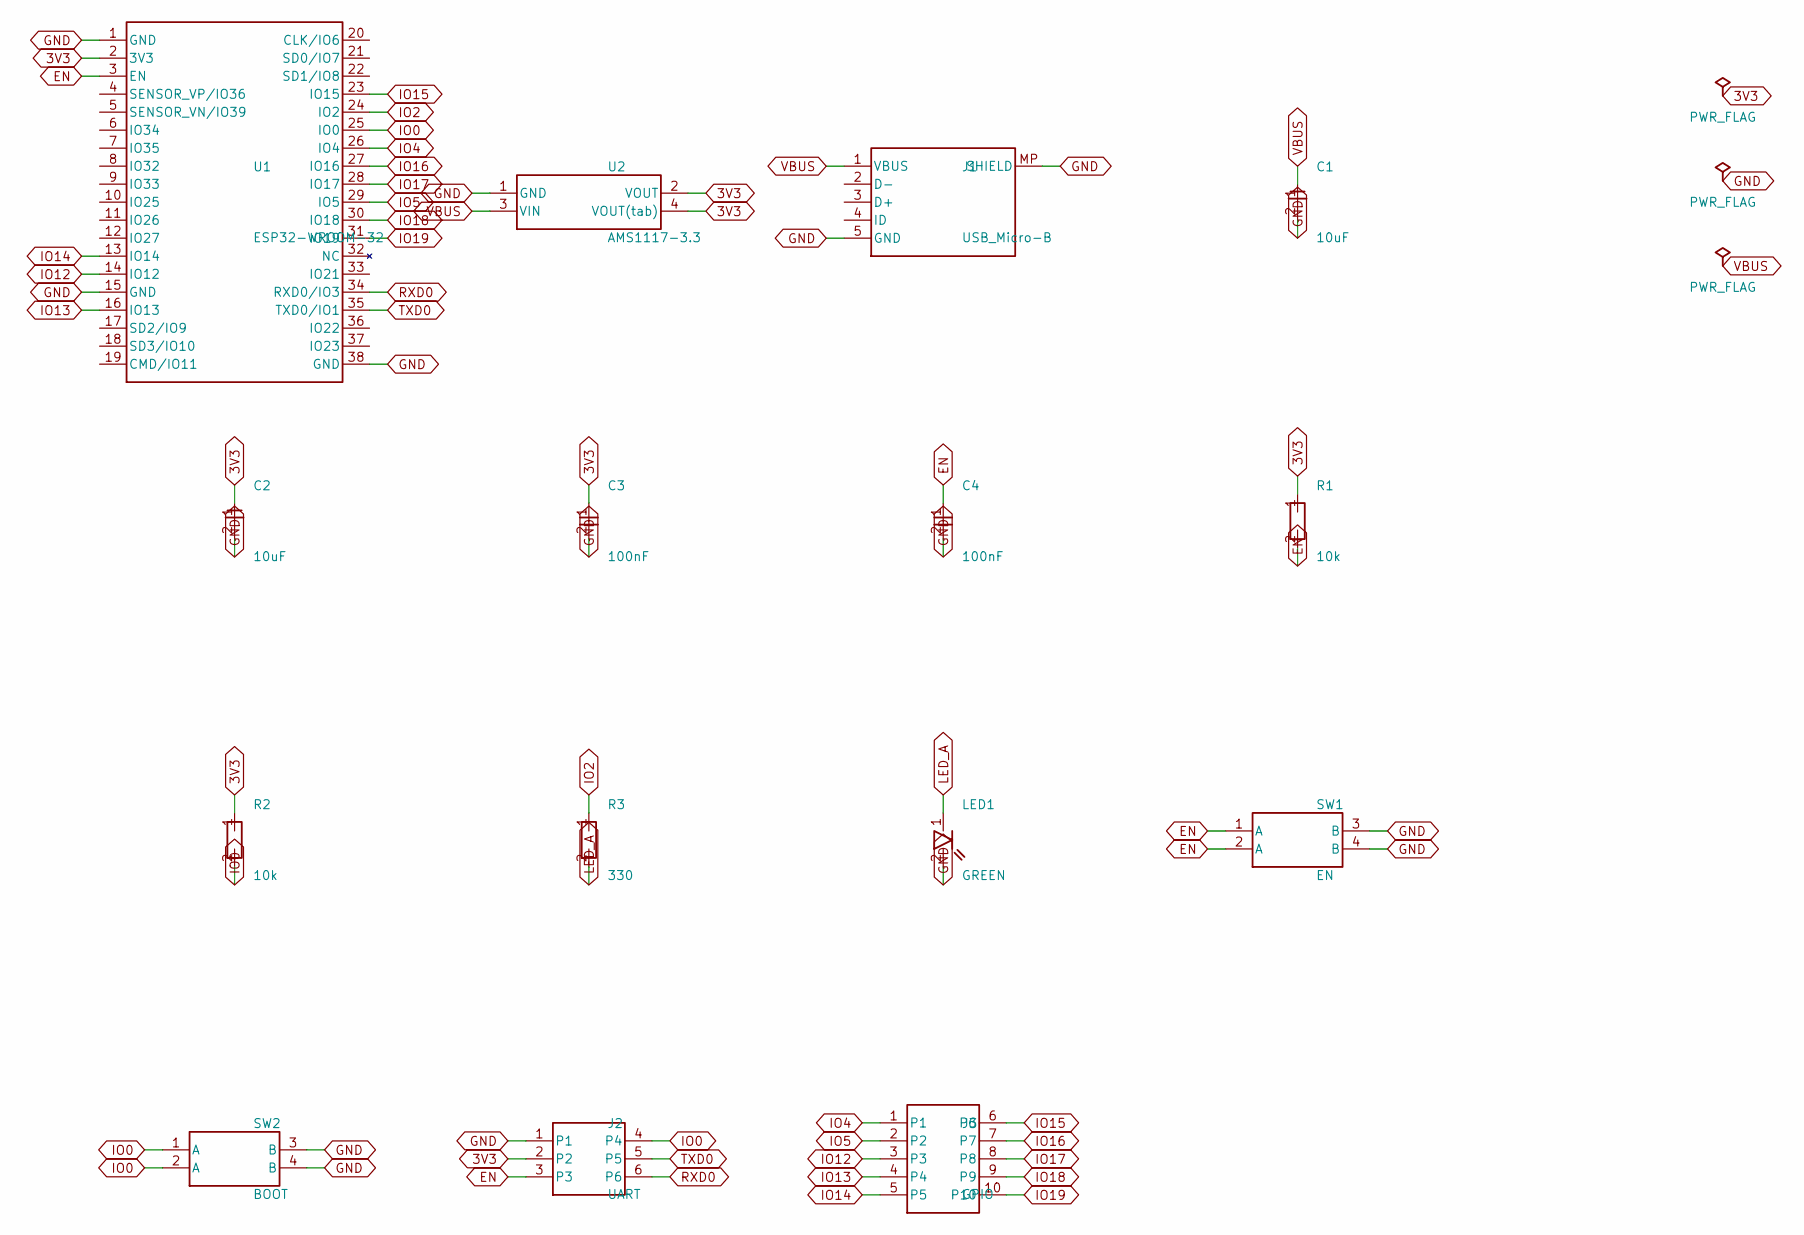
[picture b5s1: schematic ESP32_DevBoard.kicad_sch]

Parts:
C1, C2: 10uF; CP_1206
C3, C4: 100nF; C_0805
J1: USB_Micro-B
J2: UART; Header_1x06
J3: GPIO; Header_1x10
LED1: GREEN; LED_0805
R1, R2: 10k; R_0805
R3: 330; R_0805
SW1: EN; SW_Push_6mm
SW2: BOOT; SW_Push_6mm
U1: ESP32-WROOM-32
U2: AMS1117-3.3; SOT-223

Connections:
3V3: C2.1, C3.1, J2.2, R1.1, R2.1, U1.2 (3V3), U2.2 (VOUT), U2.4 (VOUT(tab))
EN: C4.1, J2.3, R1.2, SW1.1 (A), SW1.2 (A), U1.3 (EN)
GND: C1.2, C2.2, C3.2, C4.2, J1.5 (GND), J1.MP (SHIELD), J2.1, LED1.2, SW1.3 (B), SW1.4 (B), SW2.3 (B), SW2.4 (B), U1.1 (GND), U1.15 (GND), U1.38 (GND), U2.1 (GND)
IO0: J2.4, R2.2, SW2.1 (A), SW2.2 (A), U1.25 (IO0)
IO2: R3.1, U1.24 (IO2)
IO4: J3.1, U1.26 (IO4)
IO5: J3.2, U1.29 (IO5)
IO12: J3.3, U1.14 (IO12)
IO13: J3.4, U1.16 (IO13)
IO14: J3.5, U1.13 (IO14)
IO15: J3.6, U1.23 (IO15)
IO16: J3.7, U1.27 (IO16)
IO17: J3.8, U1.28 (IO17)
IO18: J3.9, U1.30 (IO18)
IO19: J3.10, U1.31 (IO19)
LED_A: LED1.1, R3.2
RXD0: J2.6, U1.34 (RXD0/IO3)
TXD0: J2.5, U1.35 (TXD0/IO1)
VBUS: C1.1, J1.1 (VBUS), U2.3 (VIN)

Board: 2 copper layers, 15 parts (0 on the bottom side), 19 nets, no tracks yet.
